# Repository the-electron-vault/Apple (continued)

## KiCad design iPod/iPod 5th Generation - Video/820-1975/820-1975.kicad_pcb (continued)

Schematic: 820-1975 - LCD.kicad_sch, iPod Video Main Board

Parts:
C203, C204: 10nF; MLCC-0201; Voltage 10V; Tolerance 10%; Manufacturer Part Number GRM033R71A103KA01D
C280: 1uF; MLCC-0402; Voltage 16V; Tolerance 20%; Manufacturer Part Number GRM155C81C105ME11J
C281: 220nF; MLCC-0603; Voltage 25V; Tolerance 10%; Manufacturer Part Number GCM188R71E224KA55D
C282: 220nF; MLCC-0603; Voltage 25V; Tolerance 10%; Manufacturer Part Number GCM188R71E224KA55D; not fitted
J2: FF12-32A-R11AL-3H; Manufacturer Part Number FF12-32A-R11AL-3H
L280: 22uH; VLF3010ST; Tolerance 20%; Manufacturer Part Number VLF3010ST-220MR34
Q280: CMLT3904E; SOT563; Voltage 40V; Manufacturer Part Number CMLT3904E
R126, R135, R136, R137, R209: 1M; RES-0201; Tolerance 1%; Manufacturer Part Number CRCW02011M00FNED
R280: 10K; RES-0201; Tolerance 1%; Manufacturer Part Number CRCW020110K0FNED
R281: 0; RES-0201; Tolerance Jumper; Manufacturer Part Number CRCW02010000Z0ED
R282: 3K; RES-0201; Tolerance 1%; Manufacturer Part Number CRCW02013K00FNED
R283: 47K; RES-0201; Tolerance 1%; Manufacturer Part Number CRCW020147K0FNED
R284: 100K; RES-0201; Tolerance 1%; Manufacturer Part Number CRCW0201100KFNED
R291: 27; RES-0201; Tolerance 1%; Manufacturer Part Number CRCW020127R0FNED
TP60, TP61, TP62, TP63, TP64, TP65, TP66, TP67, TP68, TP69, TP70, TP71, TP72, TP73, TP74, TP75, TP76, TP77, TP78, TP79, TP80, TP81, TP82, TP83, TP84, TP85, TP86: TP; TP-SMT
U280: TPS61061YZF; TI-S-XBGA-N8; Manufacturer Part Number TPS61061YZF

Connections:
/BKLT_ADJ: R136.1, U280.A3 (ILED); also elsewhere on the board
/BKLT_DIM_L: R137.1, R284.1; also elsewhere on the board
/BKLT_EN: R135.1, U280.A2 (EN); also elsewhere on the board
/LCD/BKLT_DIM: Q280.3 (C2), R280.2, R281.2
/LCD/BKLT_DIM_Q_B: C282.2, Q280.2 (B1), Q280.5 (B2), R281.1, R284.2
/LCD/BKLT_DIM_Q_E: Q280.1 (E1), R283.2
/LCD/BKLT_FB: R282.1, R283.1, U280.B3 (FB)
/LCD/BKLT_K: J2.30, R282.2, R291.1, TP63.1
/LCD/BKLT_OUT: C281.1, C282.1, J2.31, Q280.6 (C1), R280.1, TP62.1, U280.C1 (OUT)
/LCD/BKLT_SW: L280.2, U280.C2 (SW)
/LCD/LCD_CS_L: J2.6, TP84.1; also elsewhere on the board
/LCD/LCD_D0: J2.10, TP80.1; also elsewhere on the board
/LCD/LCD_D1: J2.11, TP79.1; also elsewhere on the board
/LCD/LCD_D2: J2.12, TP78.1; also elsewhere on the board
/LCD/LCD_D3: J2.13, TP77.1; also elsewhere on the board
/LCD/LCD_D4: J2.14, TP76.1; also elsewhere on the board
/LCD/LCD_D5: J2.15, TP75.1; also elsewhere on the board
/LCD/LCD_D6: J2.16, TP74.1; also elsewhere on the board
/LCD/LCD_D7: J2.17, TP73.1; also elsewhere on the board
/LCD/LCD_D8: J2.19, TP72.1; also elsewhere on the board
/LCD/LCD_D9: J2.20, TP71.1; also elsewhere on the board
/LCD/LCD_D10: J2.21, TP70.1; also elsewhere on the board
/LCD/LCD_D11: J2.22, TP69.1; also elsewhere on the board
/LCD/LCD_D12: J2.23, TP68.1; also elsewhere on the board
/LCD/LCD_D13: J2.24, TP67.1; also elsewhere on the board
/LCD/LCD_D14: J2.25, TP66.1; also elsewhere on the board
/LCD/LCD_D15: J2.26, TP65.1; also elsewhere on the board
/LCD/LCD_DC: J2.7, TP83.1; also elsewhere on the board
/LCD/LCD_RD_L: J2.9, TP81.1; also elsewhere on the board
/LCD/LCD_RESET_L: J2.5, TP85.1; also elsewhere on the board
/LCD/LCD_VSYNC: J2.28, TP64.1; also elsewhere on the board
/LCD/LCD_WR_L: J2.8, TP82.1; also elsewhere on the board
/LCD_DETECT_A: J2.32, R126.2, TP61.1; also elsewhere on the board
/LCD_DETECT_B: J2.1, R209.2, TP86.1; also elsewhere on the board
GND: C203.2, C204.2, C280.2, C281.2, J2.4, J2.18, J2.27, J2.29, Q280.4 (E2), R135.2, R136.2, R137.2, R291.2, U280.A1 (GND), U280.C3 (PGND); also elsewhere on the board
PP_1V8_SYS: C203.1, J2.3, R126.1, R209.1; also elsewhere on the board
PP_3V_LCD: C204.1, J2.2; also elsewhere on the board
PP_SYS_MAIN: C280.1, L280.1, TP60.1, U280.B1 (VIN); also elsewhere on the board

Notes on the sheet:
DESIGN NOTE: Q280 is likely used to facilitate the idle dimming function of the display. When BKLT_DIM_L is low, Q280A is turned on via R280, and connects R283 to the LED driver's output, less VBE. The potential divider formed by R283, R282, and R291 raises the voltage at the LED driver's FB input,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
DESIGN NOTE: R291 (${a67e2e95-2b8c-4bd2-98c8-8421fd66347b:VALUE} Ohms) sets LED current to 18.5mA.
LED_CATHODE
VSS
D11
~{WR}
~{CS}
LED_ANODE
D12
~{RES}
LD1
LD5
LD4
VDD
LD2
D13
Pinout credit - Mike Harrison @mikeselectricstuff http://www.electricstuff.co.uk/ipodlcd.html One small correction to the pinout however. The WR and RS/CD pins should be swapped, based on the fanout of the display controller to the LCD FPC. LCD Controller is likely Epson S1D19122. Pins shorted on L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
VDDI/VCORE
D10
~{RD}
LD0
D14
D15
LD7
LD3
LD6

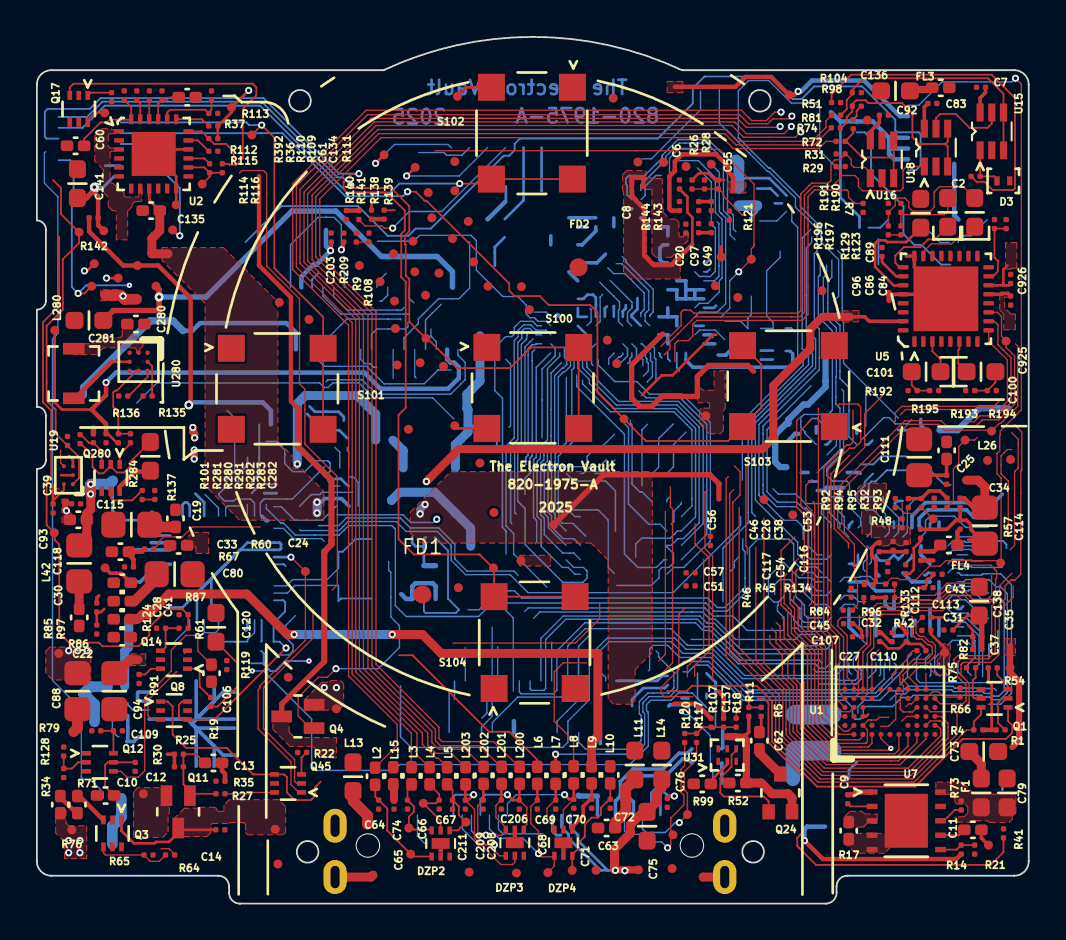
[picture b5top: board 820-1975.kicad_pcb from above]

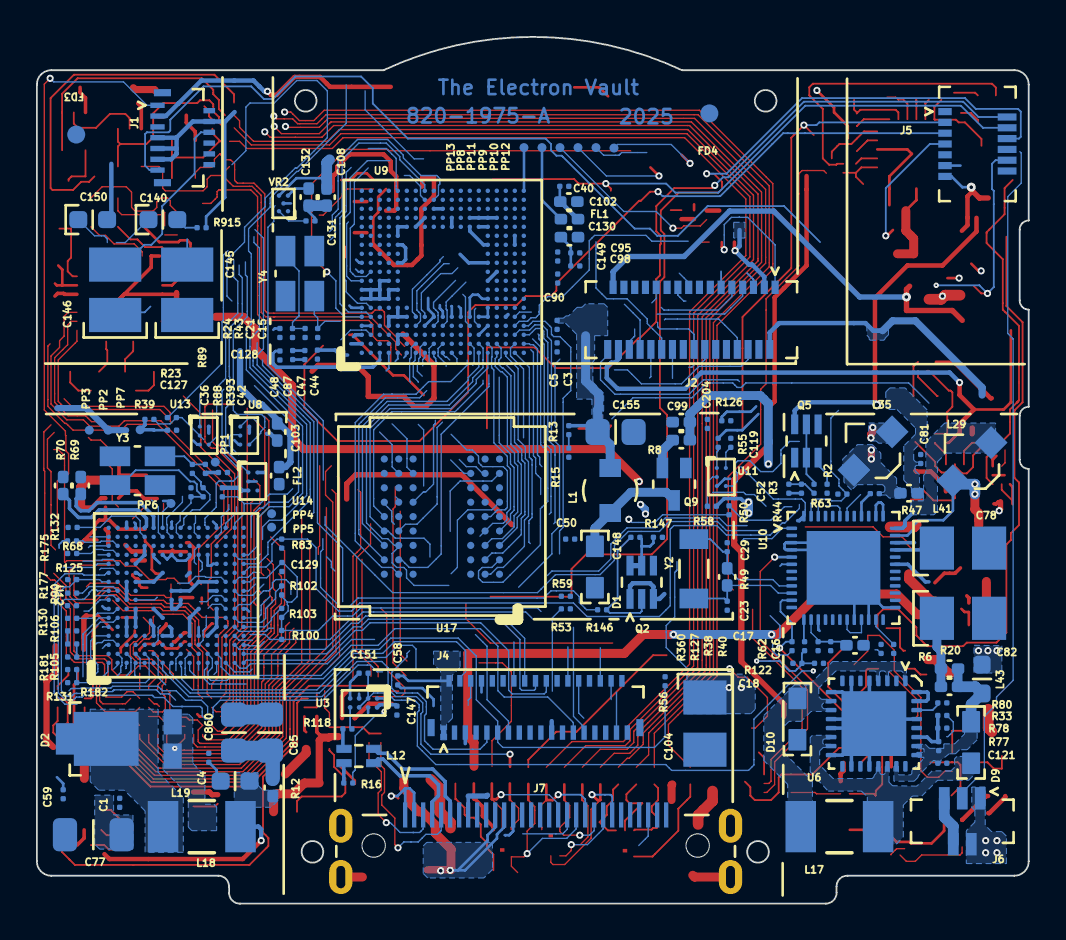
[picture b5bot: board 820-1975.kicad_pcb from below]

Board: 2 copper layers, 55.1 x 48.1 mm, 536 parts (166 on the bottom side), 365 nets.

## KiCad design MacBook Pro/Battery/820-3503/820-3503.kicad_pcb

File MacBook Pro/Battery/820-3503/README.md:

# 820-3503 A1493, A1582 BMS Board

## Overview
This is an open-source, KiCad-based 820-3503 PCBA that has been reverse-engineered from a physical board. This is the BMS used in the A1493 and A1582 battery packs for the 13" Retina MacBook Pro.

## Disclaimer
The information contained in this repository has been generated via reverse-engineering of publicly available material, and is provided without warranty or guarantee of accuracy. [The Electron Vault](https://www.theelectronvault.com/) is not responsible for any losses or damages caused to equipment as a consequence of the information contained in this repository or associated documents.

## Setup
### Database Library
This project uses a local database library for all components. As the library is linked to the project through relative pathing, it should just work once the ODBC driver is installed.
1) Install an ODBC driver. I use this one http://www.ch-werner.de/sqliteodbc/
2) [Optional] Install an SQLite database editor. I use SQLiteStudio https://sqlitestudio.pl

### Theme
This KiCad project has a number of thematic customisations. These are however completely optional and everything *should* work fine with the default theme. If you however wish to install the theme, here is the procedure:
1) Install KiCad as normal.
2) Copy PREF/color/Black and White.json from the repo into the corresponding folder in your KiCad preferences.
3) Launch KiCad and open Preferences -> Colors.
4) The Black and White theme should now be available in Schematic Editor -> Colors and PCB Editor -> Colors.
5) Schematic font: Arial

## Known Limitations
As this is a reverse-engineered design, there are several limitations potentially affecting accuracy that must be acknowledged:
- **This board is not ready for production.** The intent was to make it visually accurate enough to assist with troubleshooting, repair, or as a reference design to facilitate the design of drop-in replacements or other similar projects. OpenBoardView (Landrex-BRD) compatible files (generated using [kicad-boardview](https://github.com/whitequark/kicad-boardview) exporter) are provided in the repo along with PDF schematics.
	- Component placement is only photographically accurate - there may be mechanical interferences.
	- Board outline is best-effort. Use at your own risk.
	- Some effort has been made to recover the board stackup. A partial section view can be found in DOC\Stackup.jpg. Initially it was thought to be a 4-layer stackup, however after backlit inspection, it is more likely 6. The dielectric thickness surrounding the innermost two layers was not able to be recovered, however the laminated gap beneath the top and bottom layers appears to be approximately 110um.
	- All routing is best-effort **and incomplete**, primarily as a checklist aid/sanity check that nets have been assigned to the correct components. There are missing elements such as internal planes/poly-pours.
	- Trace widths are purely photographically scaled.
- Passive component (resistors, capacitors) values were measured with an LCR meter and rounded to the nearest standard value. Accuracy is not guaranteed.
- There is a component between the power path MOSFETs that's presumed to be an NTC due to how its resistance changes (decreases) when heated. The placement location also leads credence to this assumption. The measured resistance at 'room' temperature is approximately 28.9kOhms, so it is captured in the schematic/BOM as a 30kOhm NTC. The exact part number is however unknown.
- The NXP PH1530CL power path MOSFETs are EOL and thus a datasheet could not be found (Internet Archive and other similar services were consulted). The Digi-Key listing however does indicate a 30V VDS in the description. Based on the SCR fuse rating, the drain current can be no less than 15A. If replacements are required for repairs, this should provide a starting point.

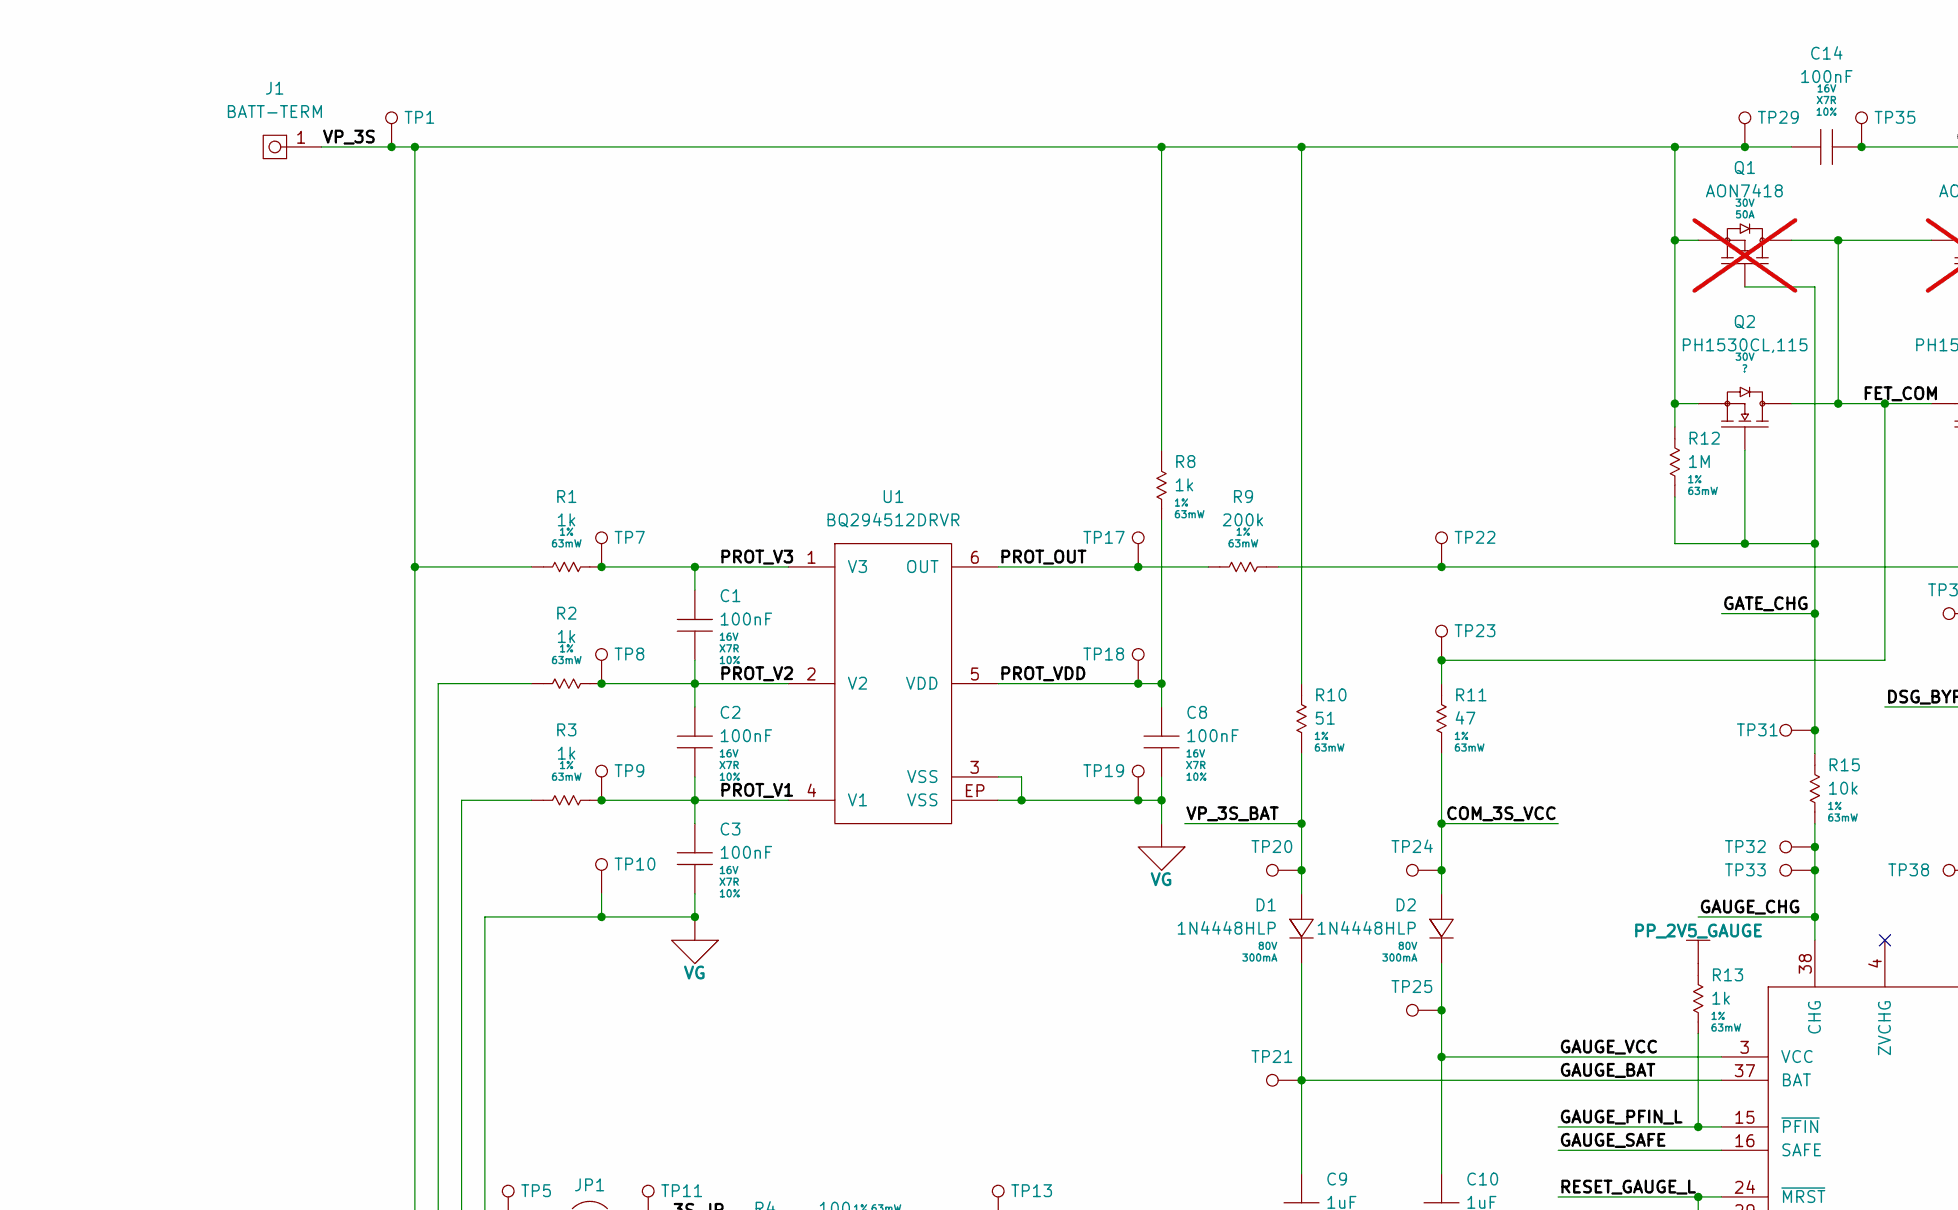
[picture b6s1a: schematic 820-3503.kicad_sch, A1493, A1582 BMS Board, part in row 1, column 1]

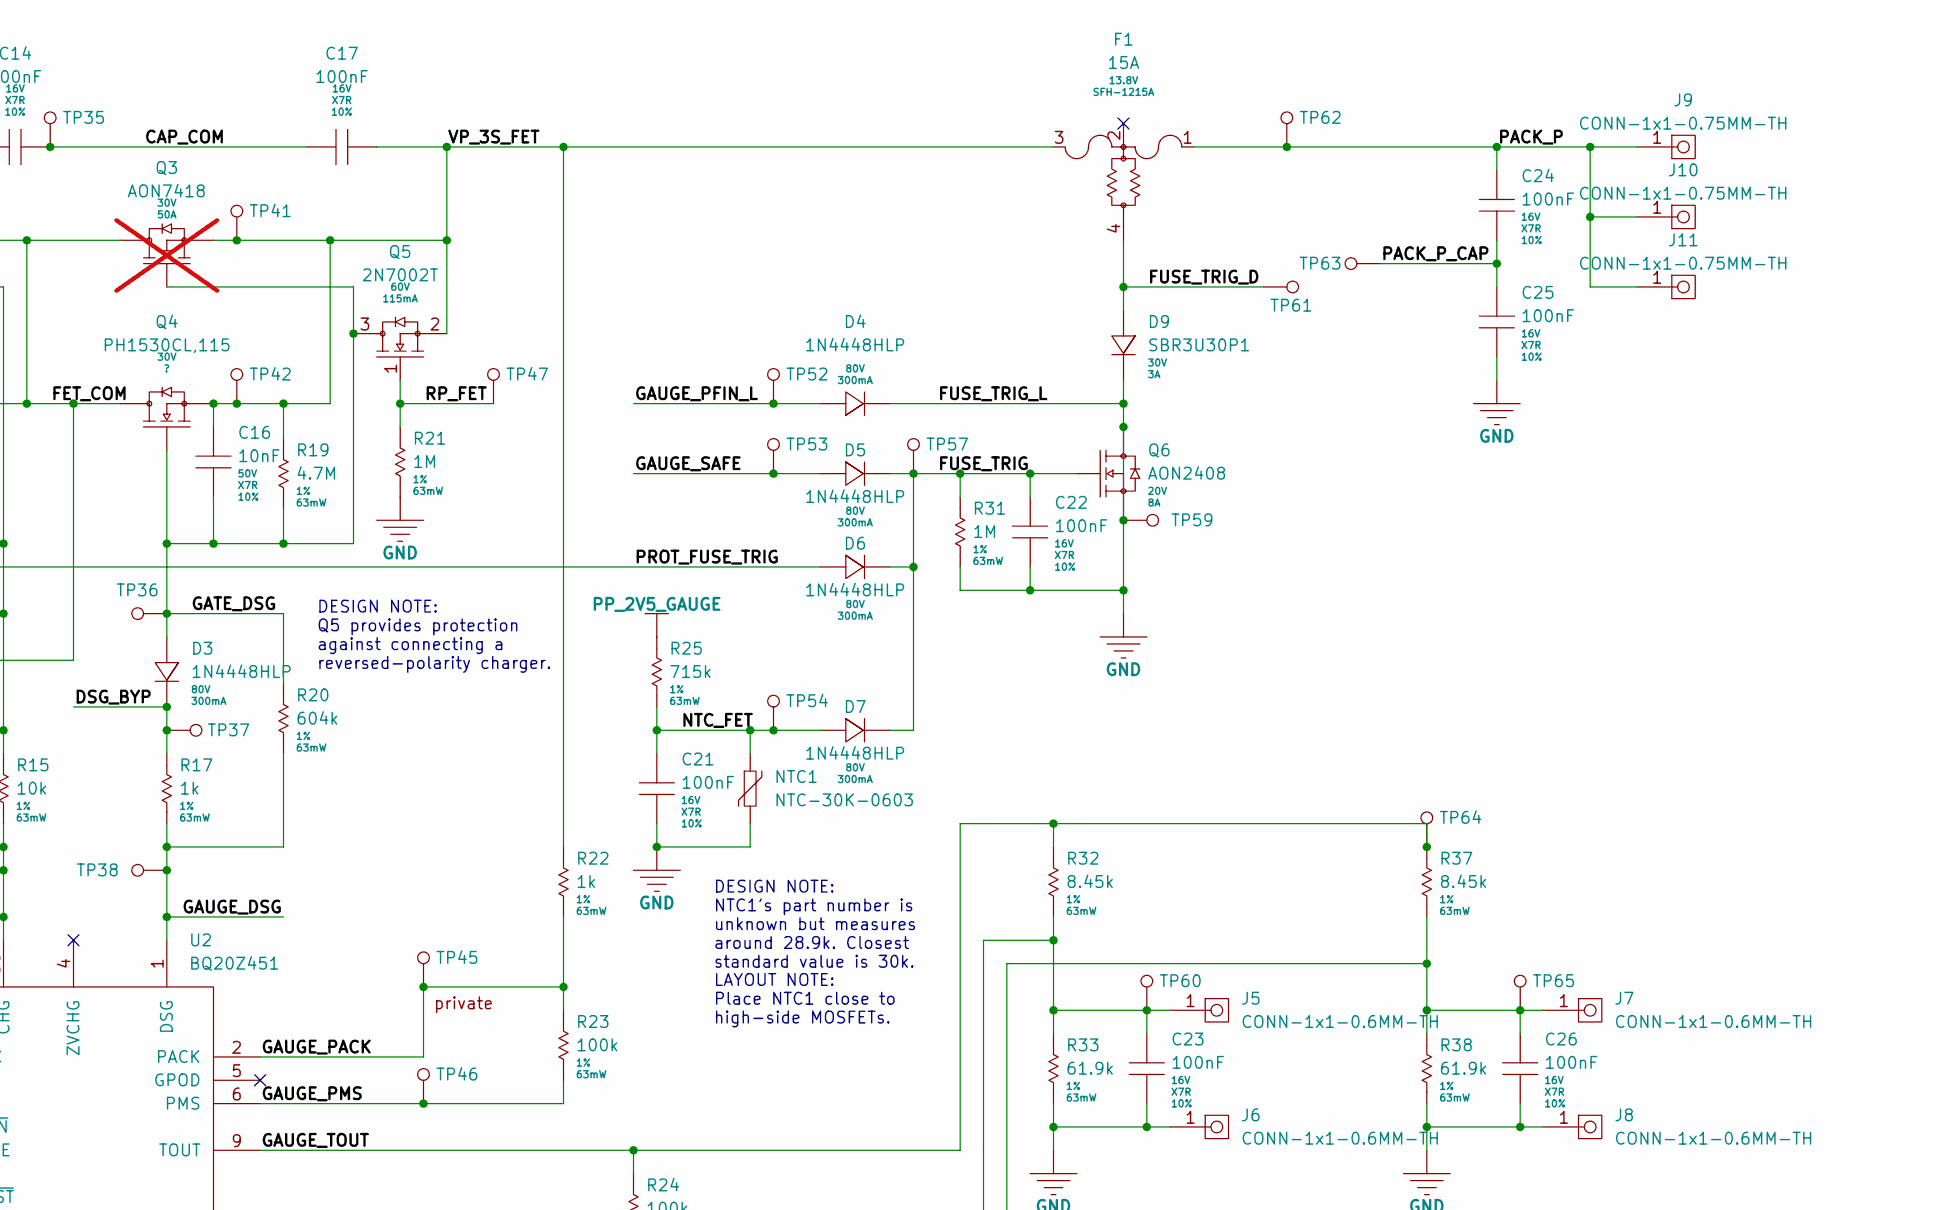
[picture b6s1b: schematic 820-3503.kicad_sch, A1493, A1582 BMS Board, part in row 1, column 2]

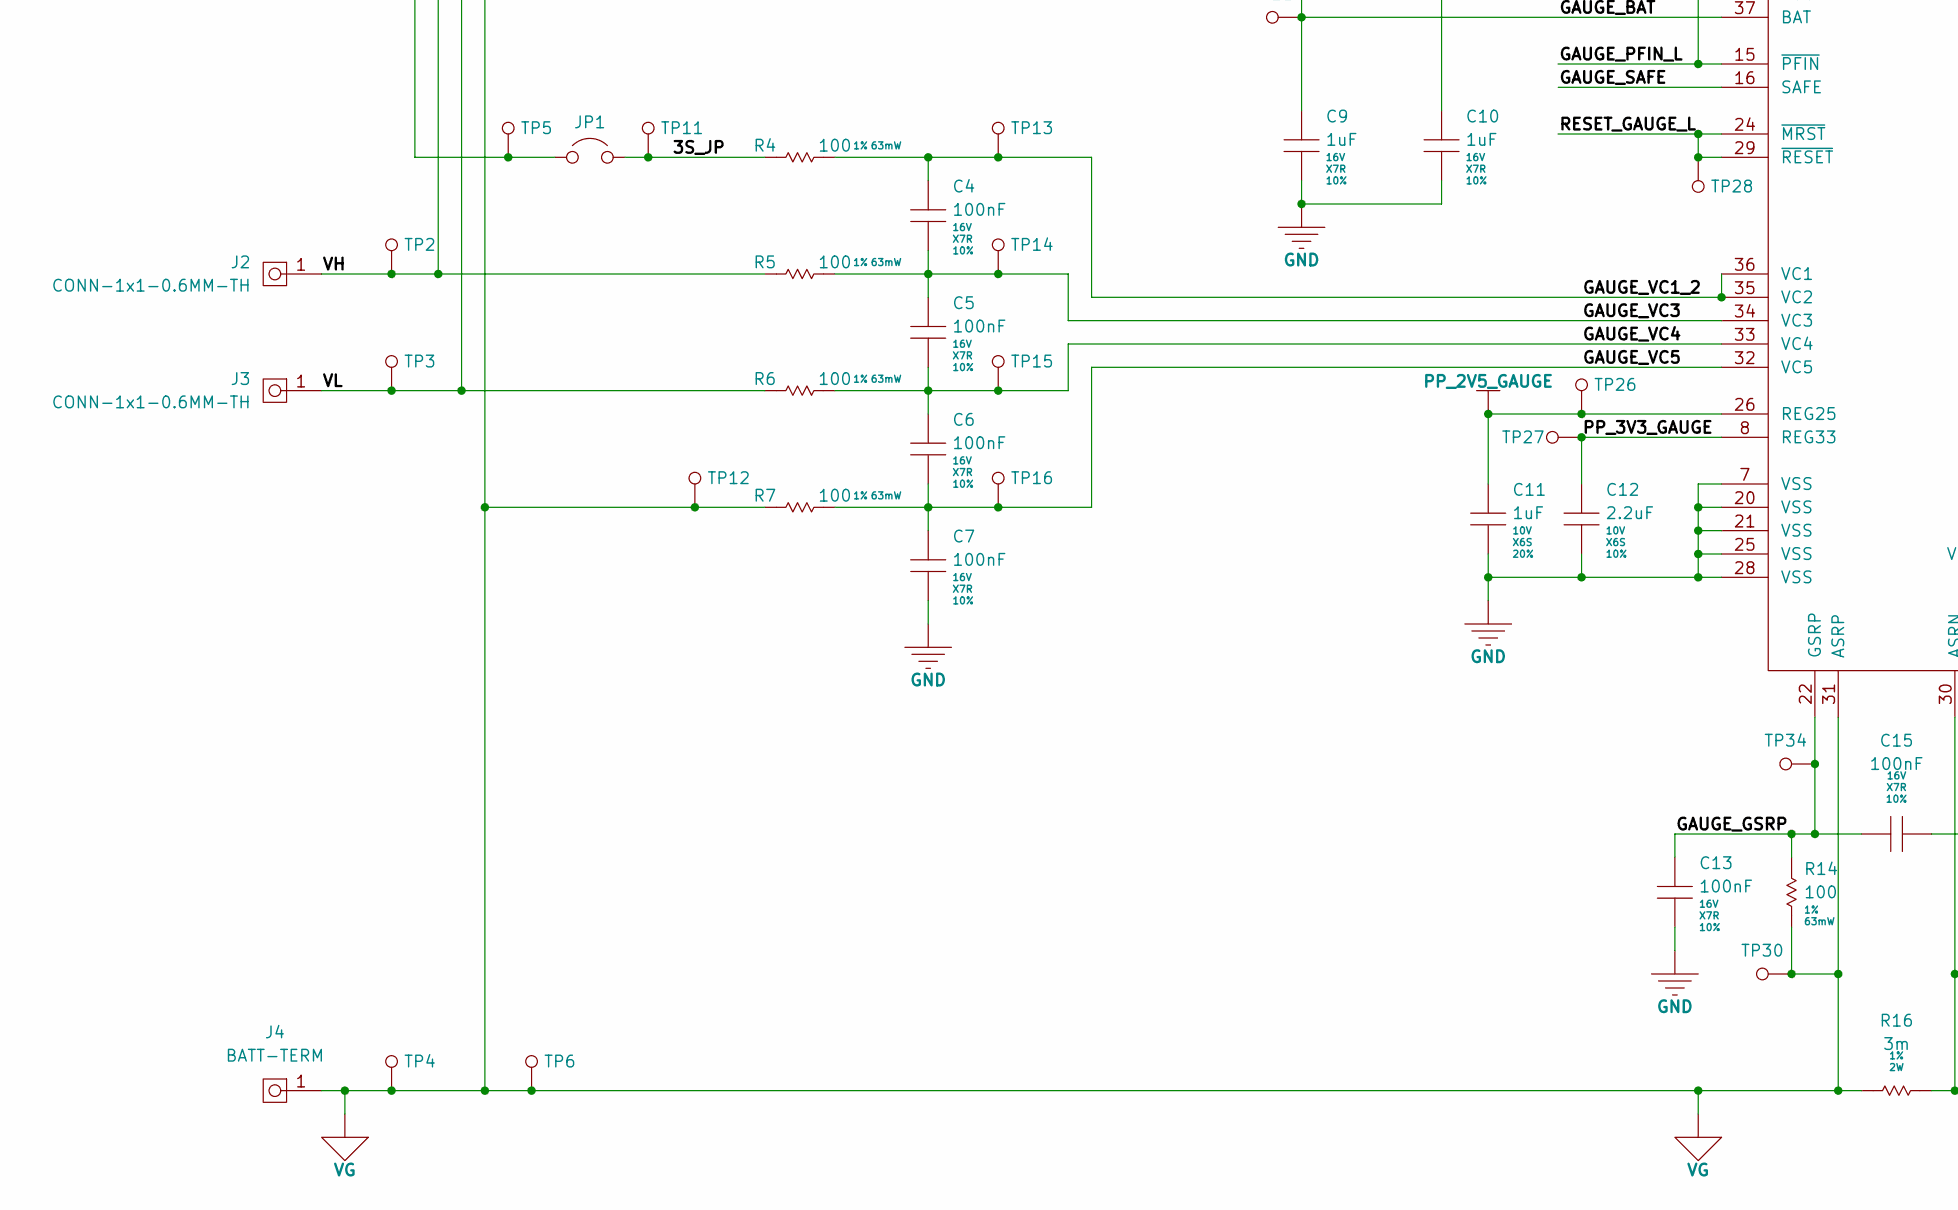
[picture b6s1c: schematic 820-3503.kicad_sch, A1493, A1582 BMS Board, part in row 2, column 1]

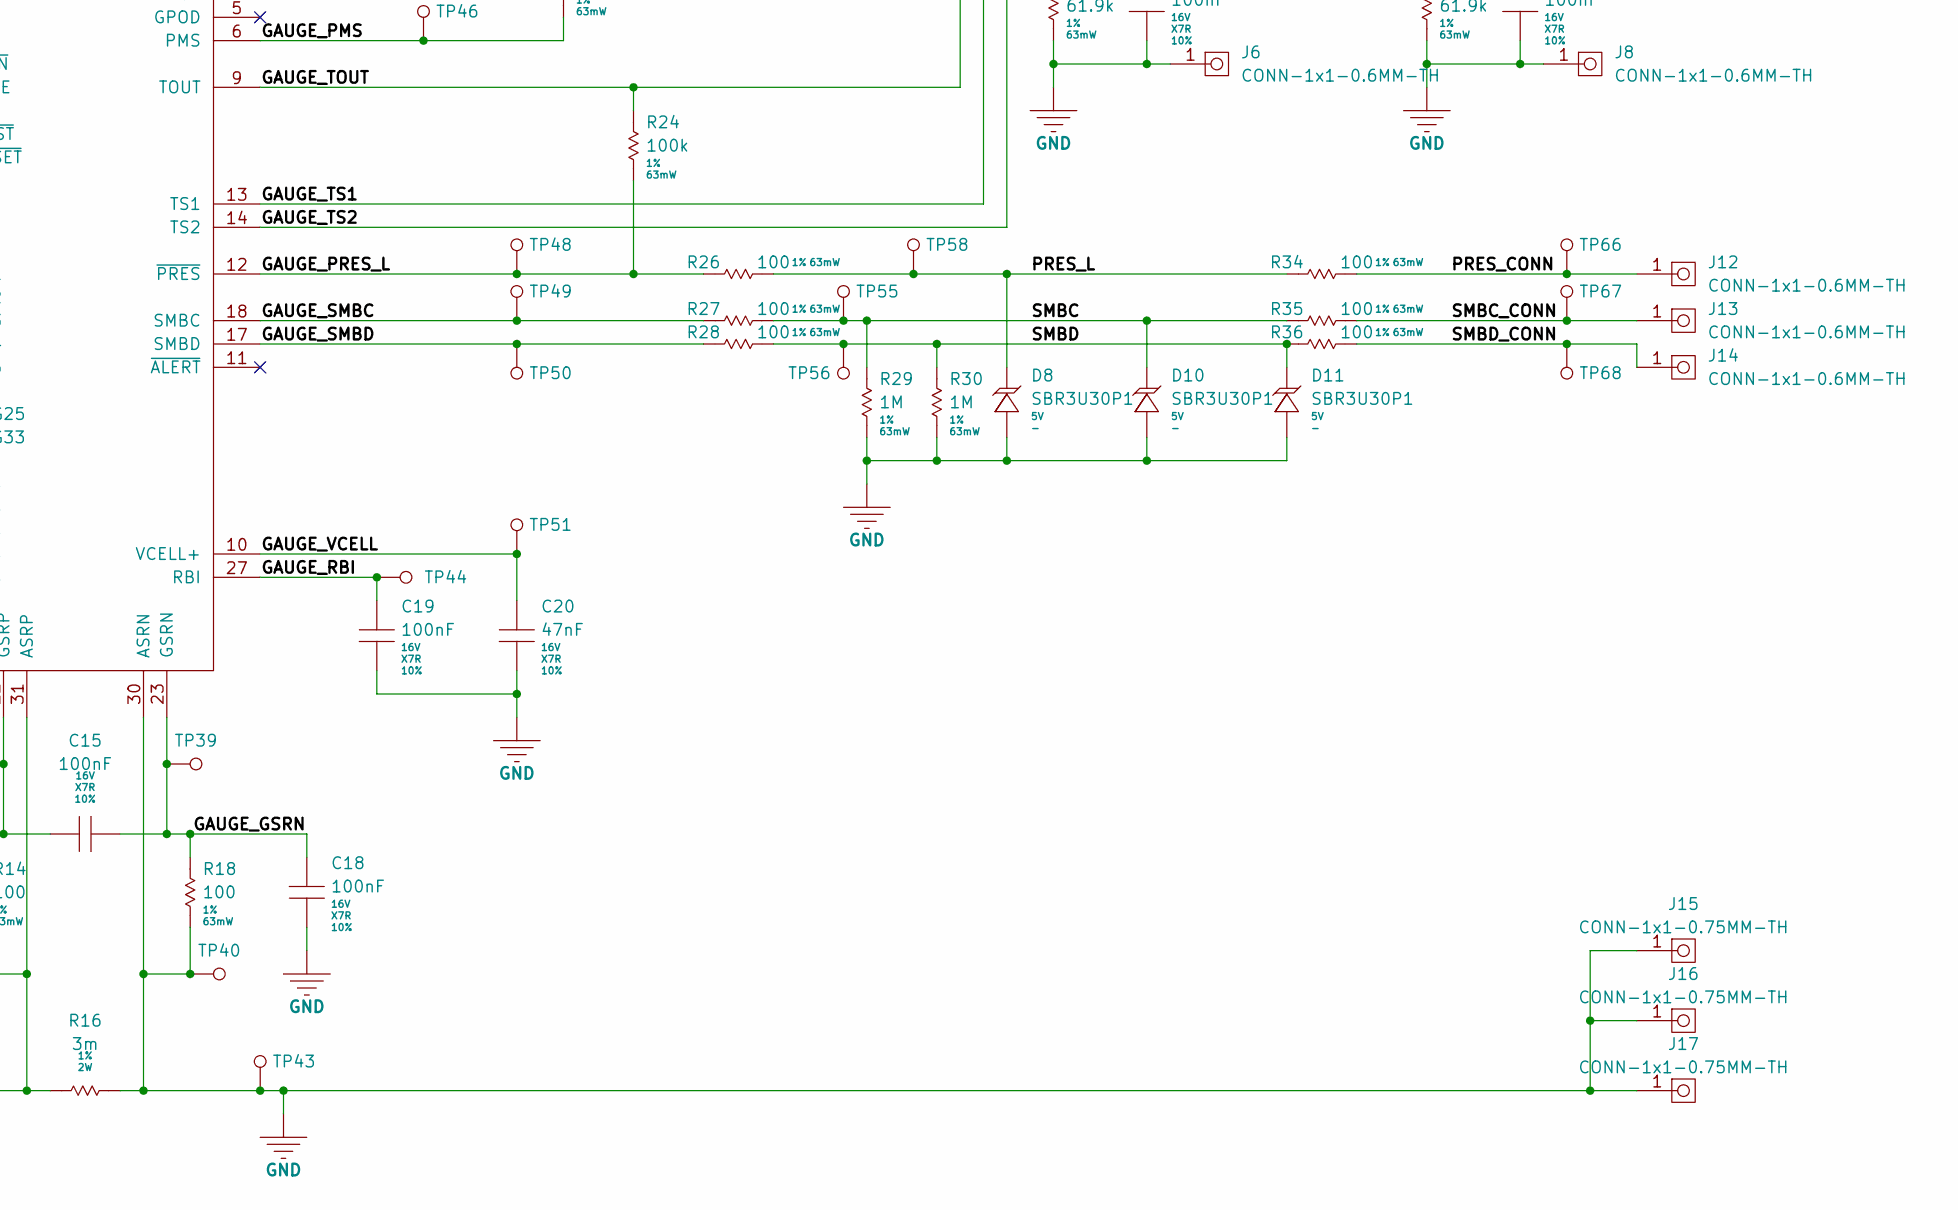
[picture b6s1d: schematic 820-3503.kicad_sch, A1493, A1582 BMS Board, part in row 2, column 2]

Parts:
C1, C2, C3, C4, C5, C6, C7, C8, C13, C14, C15, C17, C18, C19, C21, C22, C23, C24, C25, C26: 100nF; MLCC-0402; Voltage 16V; Tolerance 10%; Manufacturer Part Number GCM155R71C104KA55J
C9, C10: 1uF; MLCC-0603; Voltage 16V; Tolerance 10%; Manufacturer Part Number CL10B105KO8NNNC
C11: 1uF; MLCC-0402; Voltage 10V; Tolerance 20%; Manufacturer Part Number GRM155C81A105MA12D
C12: 2.2uF; MLCC-0402; Voltage 10V; Tolerance 10%; Manufacturer Part Number GRM155C81A225KE44D
C16: 10nF; MLCC-0402; Voltage 50V; Tolerance 10%; Manufacturer Part Number C0402C103K5RACTU
C20: 47nF; MLCC-0402; Voltage 16V; Tolerance 10%; Manufacturer Part Number GRM155R71C473KA01J
D1, D2, D3, D4, D5, D6, D7: 1N4448HLP; SOD-882; Voltage 80V; Manufacturer Part Number 1N4448HLP
D8, D10, D11: SBR3U30P1; SOD-882; Voltage 5V; Manufacturer Part Number SBR3U30P1
D9: SBR3U30P1; PowerDI123; Voltage 30V; Manufacturer Part Number SBR3U30P1
F1: 15A; SFH-1215A; Voltage 13.8V; Manufacturer Part Number SFH-1215A
J1, J4: BATT-TERM; Manufacturer Part Number BATT-TERM
J2, J3, J5, J6, J7, J8, J12, J13, J14: CONN-1x1-0.6MM-TH; TH-1.2x0.6; Manufacturer Part Number CONN-1x1-0.6MM-TH
J9, J10, J11, J15, J16, J17: CONN-1x1-0.75MM-TH; TH-1.4x0.75; Manufacturer Part Number CONN-1x1-0.75MM-TH
JP1: JUMPER-NO
NTC1: NTC-30K-0603; MLCC-0603; Manufacturer Part Number NTC-30K-0603
Q1, Q3: AON7418; DFN3333; Voltage 30V; Manufacturer Part Number AON7418; not fitted
Q2, Q4: PH1530CL,115; LFPAK56; Voltage 30V; Manufacturer Part Number PH1530CL,115
Q5: 2N7002T; SOT-523; Voltage 60V; Manufacturer Part Number 2N7002T
Q6: AON2408; DFN-2x2B; Voltage 20V; Manufacturer Part Number AON2408
R1, R2, R3, R8, R13, R17, R22: 1k; RES-0402; Tolerance 1%; Manufacturer Part Number CRCW04021K00FKED
R4, R5, R6, R7, R14, R18, R26, R27, R28, R34, R35, R36: 100; RES-0402; Tolerance 1%; Manufacturer Part Number CRCW0402100RFKED
R9: 200k; RES-0402; Tolerance 1%; Manufacturer Part Number CRCW0402200KFKED
R10: 51; RES-0402; Tolerance 1%; Manufacturer Part Number CRCW040251R0FKED
R11: 47; RES-0402; Tolerance 1%; Manufacturer Part Number CRCW040247R0FKED
R12, R21, R29, R30, R31: 1M; RES-0402; Tolerance 1%; Manufacturer Part Number CRCW04021M00FKED
R15: 10k; RES-0402; Tolerance 1%; Manufacturer Part Number CRCW040210K0FKED
R16: 3m; RES-2512; Tolerance 1%; Manufacturer Part Number CRF2512-FZ-R003ELF
R19: 4.7M; RES-0402; Tolerance 1%; Manufacturer Part Number CRCW04024M70FKED
R20: 604k; RES-0402; Tolerance 1%; Manufacturer Part Number CRCW0402604KFKED
R23, R24: 100k; RES-0402; Tolerance 1%; Manufacturer Part Number CRCW0402100KFKED
R25: 715k; RES-0402; Tolerance 1%; Manufacturer Part Number CRCW0402715KFKED
R32, R37: 8.45k; RES-0402; Tolerance 1%; Manufacturer Part Number CRCW04028K45FKED
R33, R38: 61.9k; RES-0402; Tolerance 1%; Manufacturer Part Number CRCW040261K9FKED
TP1, TP4, TP14, TP19, TP24, TP28, TP30, TP34, TP35, TP39, TP40, TP42, TP43, TP44, TP45, TP46, TP48, TP61, TP62, TP63, TP64: TP; TP-SMT-0.6mm
TP2, TP3, TP5, TP6, TP7, TP8, TP9, TP10, TP11, TP12, TP13, TP15, TP16, TP17, TP18, TP20, TP21, TP22, TP23, TP25, TP26, TP27, TP29, TP31, TP32, TP33, TP36, TP37, TP38, TP41, TP47, TP49, TP50, TP51, TP52, TP53, TP54, TP55, TP56, TP57, TP58, TP59, TP60, TP65, TP66, TP67, TP68: TP; TP-TH-0.6mm
U1: BQ294512DRVR; DRV0006A; Manufacturer Part Number BQ294512DRVR
U2: BQ20Z451; TSSOP-38-0.5; Manufacturer Part Number BQ20Z451

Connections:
/3S_JP: JP1.2, R4.1, TP11.1
/CAP_COM: C14.2, C17.1, TP35.1
/COM_3S_VCC: D2.A, R11.2, TP24.1
/DSG_BYP: D3.K, R17.1, TP37.1
/FET_COM: Q1.D, Q2.D, Q3.D, Q4.D, R11.1, TP23.1
/FUSE_TRIG: C22.1, D5.K, D6.K, D7.K, Q6.G, R31.1, TP57.1
/FUSE_TRIG_D: D9.A, F1.4 (HEAT2), TP61.1
/GATE_CHG: Q1.G, Q2.G, R12.2, R15.1, TP31.1
/GATE_DSG: C16.2, D3.A, Q3.G, Q4.G, Q5.3 (D), R19.2, R20.1, TP36.1
/GAUGE_BAT: C9.1, D1.K, TP21.1, U2.37 (BAT)
/GAUGE_CHG: R15.2, TP32.1, TP33.1, U2.38 (CHG)
/GAUGE_DSG: R17.2, R20.2, TP38.1, U2.1 (DSG)
/GAUGE_GSRN: C15.2, C18.1, R18.1, TP39.1, U2.23 (GSRN)
/GAUGE_GSRP: C13.1, C15.1, R14.1, TP34.1, U2.22 (GSRP)
/GAUGE_PACK: R22.2, R23.1, TP45.1, U2.2 (PACK)
/GAUGE_PFIN_L: D4.A, R13.2, TP52.1, U2.15 (~PFIN)
/GAUGE_PMS: R23.2, TP46.1, U2.6 (PMS)
/GAUGE_PRES_L: R24.2, R26.1, TP48.1, U2.12 (~PRES)
/GAUGE_RBI: C19.1, TP44.1, U2.27 (RBI)
/GAUGE_SAFE: D5.A, TP53.1, U2.16 (SAFE)
/GAUGE_SMBC: R27.1, TP49.1, U2.18 (SMBC)
/GAUGE_SMBD: R28.1, TP50.1, U2.17 (SMBD)
/GAUGE_TOUT: R24.1, R32.1, R37.1, TP64.1, U2.9 (TOUT)
/GAUGE_TS1: C23.1, J5.1, R32.2, R33.1, TP60.1, U2.13 (TS1)
/GAUGE_TS2: C26.1, J7.1, R37.2, R38.1, TP65.1, U2.14 (TS2)
/GAUGE_VC1_2: C4.1, R4.2, TP13.1, U2.35 (VC2), U2.36 (VC1)
/GAUGE_VC3: C4.2, C5.1, R5.2, TP14.1, U2.34 (VC3)
/GAUGE_VC4: C5.2, C6.1, R6.2, TP15.1, U2.33 (VC4)
/GAUGE_VC5: C6.2, C7.1, R7.2, TP16.1, U2.32 (VC5)
/GAUGE_VCC: C10.1, D2.K, TP25.1, U2.3 (VCC)
/GAUGE_VCELL: C20.1, TP51.1, U2.10 (VCELL+)
/NTC_FET: C21.1, D7.A, NTC1.1, R25.2, TP54.1
/PACK_P: C24.1, F1.1 (FUSE1), J9.1, J10.1, J11.1, TP62.1
/PACK_P_CAP: C24.2, C25.1, TP63.1
/PP_3V3_GAUGE: C12.1, TP27.1, U2.8 (REG33)
/PRES_CONN: J12.1, R34.2, TP66.1
/PRES_L: D8.K, R26.2, R34.1, TP58.1
/PROT_FUSE_TRIG: D6.A, R9.2, TP22.1
/PROT_OUT: R9.1, TP17.1, U1.6 (OUT)
/PROT_V1: C2.2, C3.1, R3.2, TP9.1, U1.4 (V1)
/PROT_V2: C1.2, C2.1, R2.2, TP8.1, U1.2 (V2)
/PROT_V3: C1.1, R1.2, TP7.1, U1.1 (V3)
/PROT_VDD: C8.1, R8.2, TP18.1, U1.5 (VDD)
/RESET_GAUGE_L: TP28.1, U2.24 (~MRST), U2.29 (~RESET)
/RP_FET: Q5.1 (G), R21.1, TP47.1
/SMBC: D10.K, R27.2, R29.1, R35.1, TP55.1
/SMBC_CONN: J13.1, R35.2, TP67.1
/SMBD: D11.K, R28.2, R30.1, R36.1, TP56.1
/SMBD_CONN: J14.1, R36.2, TP68.1
/VH: J2.1, R2.1, R5.1, TP2.1
/VL: J3.1, R3.1, R6.1, TP3.1
/VP_3S: C14.1, J1.1, JP1.1, Q1.S, Q2.S, R1.1, R8.1, R10.1, R12.1, TP1.1, TP5.1, TP29.1
/VP_3S_BAT: D1.A, R10.2, TP20.1
/VP_3S_FET: C16.1, C17.2, F1.3 (FUSE2), Q3.S, Q4.S, Q5.2 (S), R19.1, R22.1, TP41.1, TP42.1
GND: C7.2, C9.2, C10.2, C11.2, C12.2, C13.2, C18.2, C19.2, C20.2, C21.2, C22.2, C23.2, C25.2, C26.2, D4.K, D8.A, D9.K, D10.A, D11.A, J6.1, J8.1, J15.1, J16.1, J17.1, NTC1.2, Q6.D, Q6.S, R16.2, R18.2, R21.2, R29.2, R30.2, R31.2, R33.2, R38.2, TP40.1, TP43.1, TP59.1, U2.7 (VSS), U2.20 (VSS), U2.21 (VSS), U2.25 (VSS), U2.28 (VSS), U2.30 (ASRN)
PP_2V5_GAUGE: C11.1, R13.1, R25.1, TP26.1, U2.26 (REG25)
VG: C3.2, C8.2, J4.1, R7.1, R14.2, R16.1, TP4.1, TP6.1, TP10.1, TP12.1, TP19.1, TP30.1, U1.3 (VSS), U1.EP (VSS), U2.31 (ASRP)

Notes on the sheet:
DESIGN NOTE: NTC1's part number is unknown but measures around 28.9k. Closest standard value is 30k.
LAYOUT NOTE: Place NTC1 close to high-side MOSFETs.
DESIGN NOTE: Q5 provides protection against connecting a reversed-polarity charger.

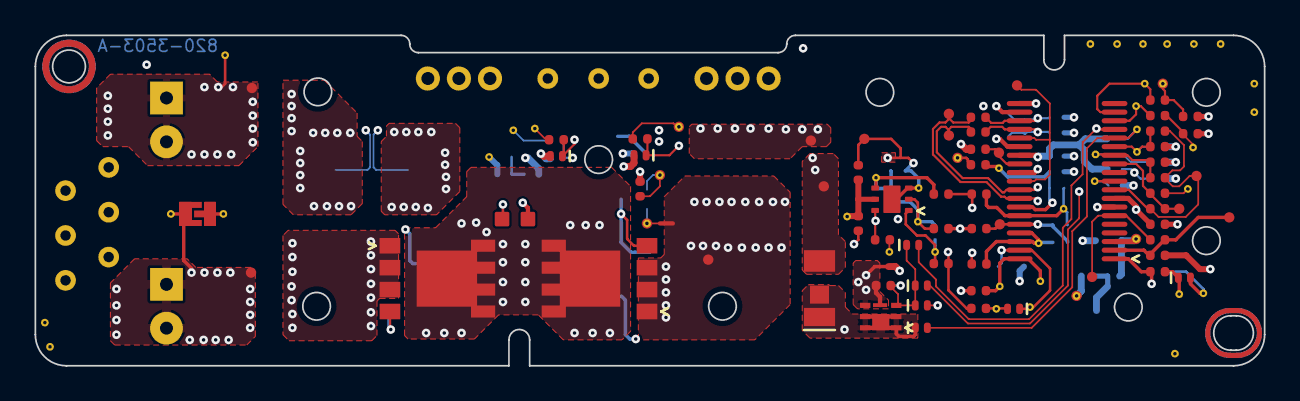
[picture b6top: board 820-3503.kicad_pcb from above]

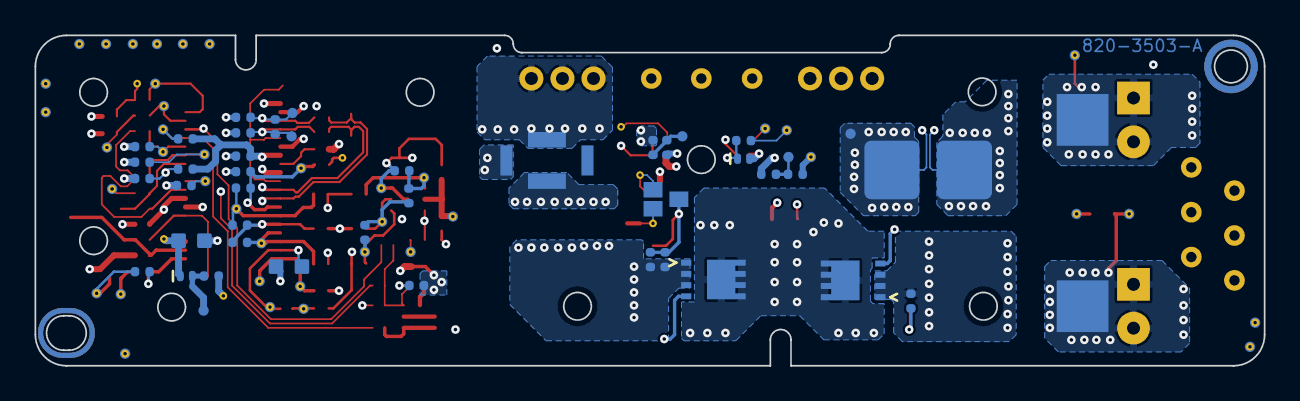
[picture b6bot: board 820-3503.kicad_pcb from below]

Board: 6 copper layers, 71.2 x 19.2 mm, 171 parts (85 on the bottom side), 57 nets.
